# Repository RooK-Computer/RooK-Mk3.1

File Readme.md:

# RooK Mk3.1

RooK is a retro gaming console based on the Raspberry PI CM4/CM5. It has all the peripherials you need to be used as an old (modernish) console:

* HDMI for audio and video out.
* Barrel jack for 5V power input, because we love the simplicity of barrel jacks.
* an audio jack for, well... speakers!
* 4 USB ports for up to 4 modern gamepads.
* A cartridge slot!
* 3 Buttons to shut RooK down, exit the game and restart the game.

## How it all works

It's quite simple: instead of having an onboard SD card, the SD cards are installed onto separate PCBs for the cartridges. Once you put a cartridge in, RooK powers up and boots off the SD card in the cartridge.

Of course, unwrapping the SD cards can be tedious, so we built a cartridge reader.

It works out of the box with retropie, except for the three buttons. In this repository you find the software needed to enable those buttons. It's best done immediately after installing retropie, before you customize your setup.

## In this repository

There are 3 folders:

* software contains the sources for the .deb file to easily install overwatch and it's configuration. You'll find the .dep file in there as well, if you don't want to build it yourself. The source is compressed, as we have to ensure ownership and file privileges. Something git tends to ignore ;)
* PCBs contains all the designs for the PCBs involved: 
    * Cartridge - the PCB for cartridges
    * CartridgeReader - should be self-explanatory
    * KeyswitchCarrier - holds the switches for the three keys
    * Mainboard - the biggest of them.
    * Parts and CM4-Files are referenced in the aforementioned design files
* STLs contain the STL files for the case and the cartridge. You'll find our FreeCAD designs in there as well.

## I wanna build one!

Well for now, you have to produce and order the parts yourself. We're working on this. Stay tuned and keep an eye out at [rook.computer](https://rook.computer).

There is a building guide in the wiki.

## License

Unless noted otherwise this work is licensed under Creative Commons Attribution Share Alike 4.0 International.

`SPDX-License-Identifier:  CC-BY-SA-4.0`

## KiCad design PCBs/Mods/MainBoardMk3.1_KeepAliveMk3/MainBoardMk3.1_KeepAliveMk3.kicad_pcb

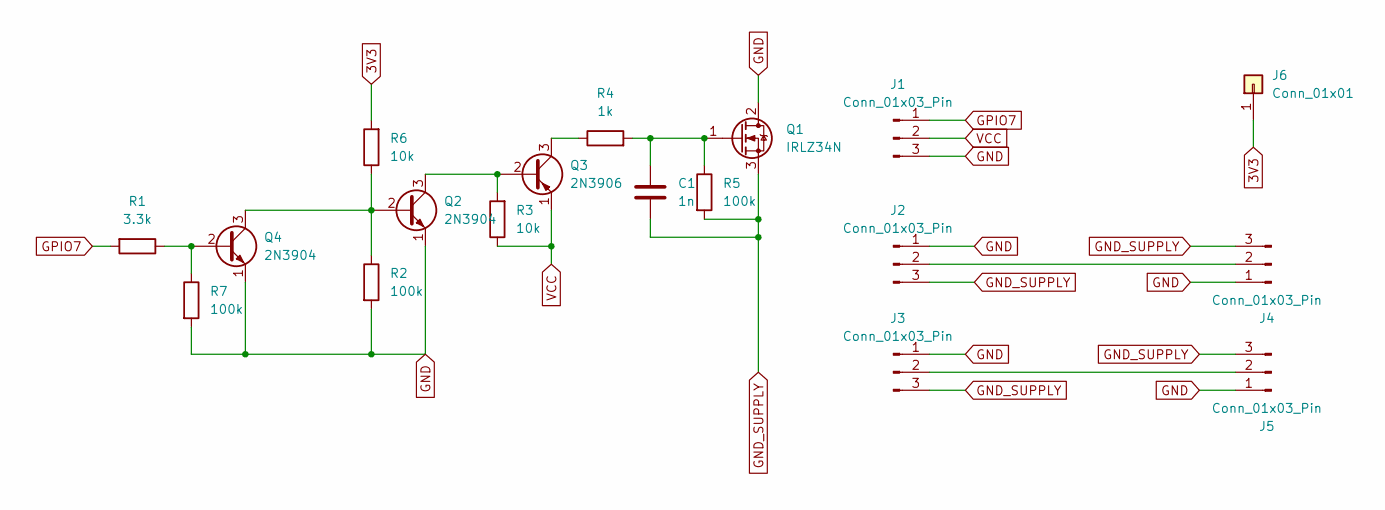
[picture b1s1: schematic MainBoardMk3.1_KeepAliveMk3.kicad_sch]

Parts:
C1: 1n; C_Disc_D5.0mm_W2.5mm_P2.50mm
J1, J2, J3: Conn_01x03_Pin; PinSocket_1x03_P2.54mm_Vertical
J4, J5: Conn_01x03_Pin; PinHeader_1x03_P2.54mm_Vertical
J6: Conn_01x01; SolderWire-0.5sqmm_1x01_D0.9mm_OD2.1mm
Q1: IRLZ34N; TO-220-3_Horizontal_TabDown
Q2, Q4: 2N3904; TO-92_HandSolder
Q3: 2N3906; TO-92_HandSolder
R1: 3.3k; R_Axial_DIN0207_L6.3mm_D2.5mm_P7.62mm_Horizontal
R2, R5, R7: 100k; R_Axial_DIN0207_L6.3mm_D2.5mm_P7.62mm_Horizontal
R3, R6: 10k; R_Axial_DIN0207_L6.3mm_D2.5mm_P7.62mm_Horizontal
R4: 1k; R_Axial_DIN0207_L6.3mm_D2.5mm_P7.62mm_Horizontal

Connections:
3V3: J6.1, R6.2
GND: J1.3, J2.1, J3.1, J4.1, J5.1, Q1.2 (D), Q2.1 (E), Q4.1 (E), R2.2, R7.2
GND_SUPPLY: C1.2, J2.3, J3.3, J4.3, J5.3, Q1.3 (S), R5.2
GPIO7: J1.1, R1.2
unnamed: J2.2, J4.2
unnamed: J3.2, J5.2
unnamed: C1.1, Q1.1 (G), R4.2, R5.1
unnamed: Q2.2 (B), Q4.3 (C), R2.1, R6.1
unnamed: Q2.3 (C), Q3.2 (B), R3.2
unnamed: Q3.3 (C), R4.1
unnamed: Q4.2 (B), R1.1, R7.1
VCC: J1.2, Q3.1 (E), R3.1

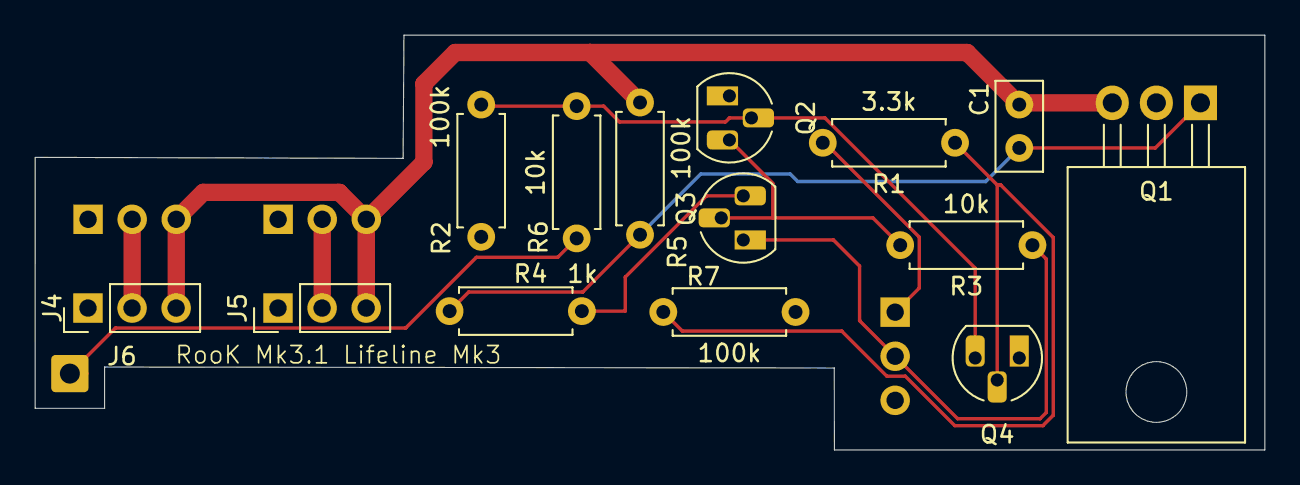
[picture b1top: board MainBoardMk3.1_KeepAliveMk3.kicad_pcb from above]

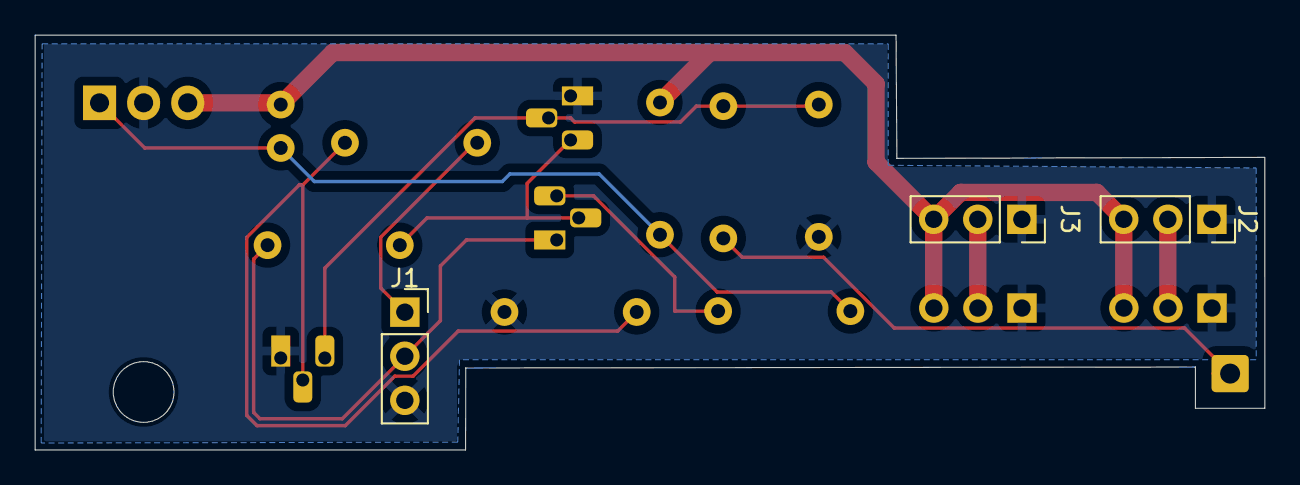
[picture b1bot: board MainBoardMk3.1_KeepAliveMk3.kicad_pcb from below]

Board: 2 copper layers, 70.8 x 23.9 mm, 18 parts (3 on the bottom side), 12 nets.

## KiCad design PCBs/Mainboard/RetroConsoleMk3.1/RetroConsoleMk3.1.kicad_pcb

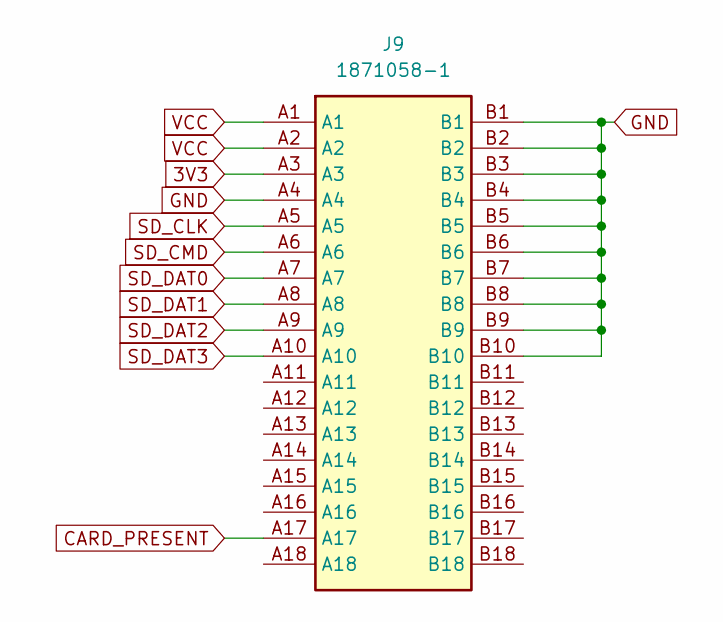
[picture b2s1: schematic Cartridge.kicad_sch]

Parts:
J9: 1871058-1; 18710581; Manufacturer_Part_Number 1871058-1; Mouser Part Number 571-1871058-1

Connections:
3V3: J9.A3; also elsewhere on the board
CARD_PRESENT: J9.A17; also elsewhere on the board
GND: J9.A4, J9.B1, J9.B2, J9.B3, J9.B4, J9.B5, J9.B6, J9.B7, J9.B8, J9.B9, J9.B10; also elsewhere on the board
SD_CLK: J9.A5; also elsewhere on the board
SD_CMD: J9.A6; also elsewhere on the board
SD_DAT0: J9.A7; also elsewhere on the board
SD_DAT1: J9.A8; also elsewhere on the board
SD_DAT2: J9.A9; also elsewhere on the board
SD_DAT3: J9.A10; also elsewhere on the board
VCC: J9.A1, J9.A2; also elsewhere on the board

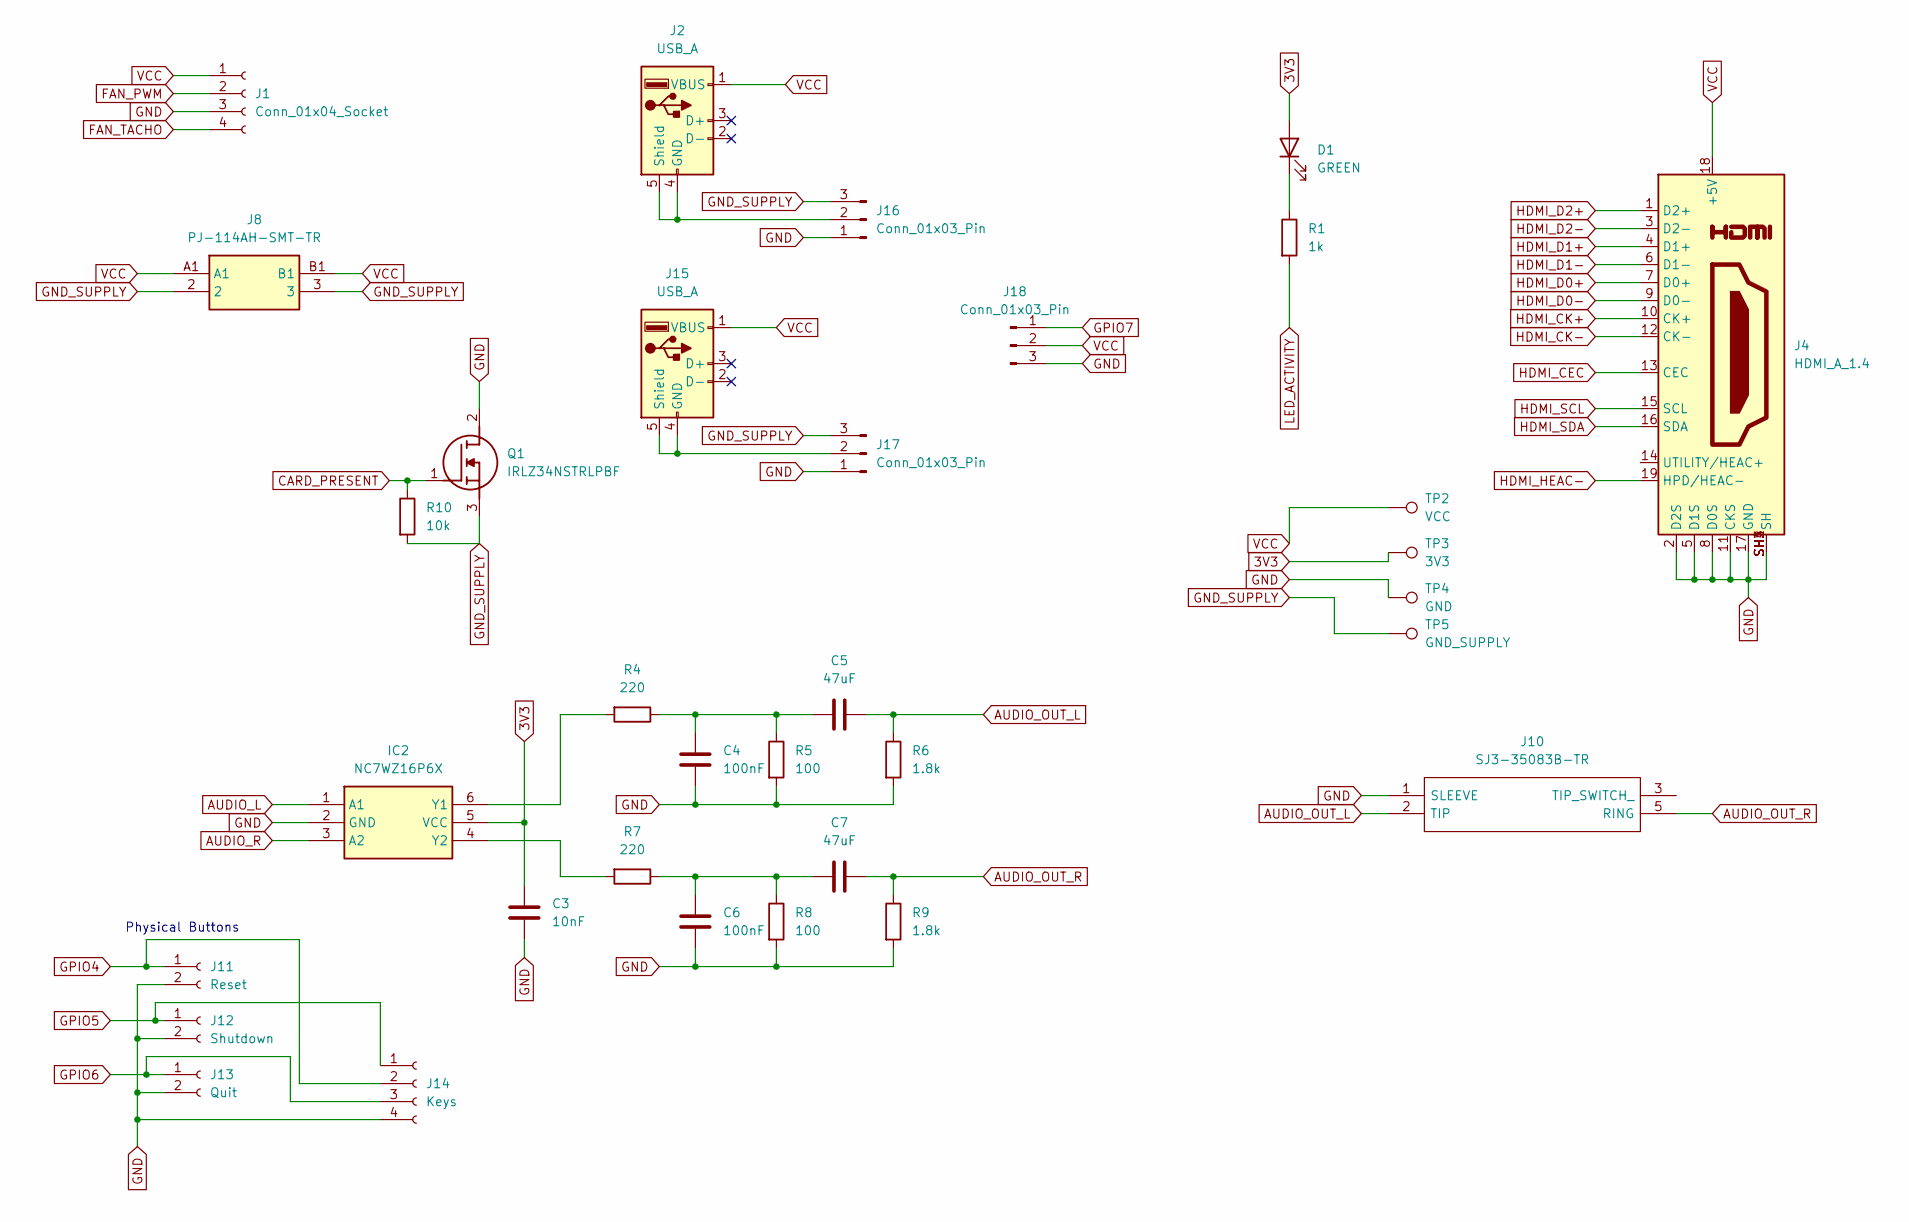
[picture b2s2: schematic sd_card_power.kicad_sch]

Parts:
C3: 10nF; C_0201_0603Metric
C4, C6: 100nF; C_0201_0603Metric
C5, C7: 47uF; C_1206_3216Metric
D1: GREEN; LED_0201_0603Metric
IC2: NC7WZ16P6X; SOT65P210X110-6N; Manufacturer_Part_Number NC7WZ16P6X; Mouser Part Number 512-NC7WZ16P6X
J1: Conn_01x04_Socket; JST_SH_BM04B-SRSS-TB_1x04-1MP_P1.00mm_Vertical
J2, J15: USB_A; USB_A_Wuerth_614004134726_Horizontal
J4: HDMI_A_1.4; HDMI_A_Molex_208658-1001_Horizontal
J8: PJ-114AH-SMT-TR; PJ114AHSMTTR; Manufacturer_Part_Number PJ-114AH-SMT-TR; Mouser Part Number 179-PJ-114AH-SMT-TR
J10: SJ3-35083B-TR; SJ335083BTR; Manufacturer_Part_Number SJ3-35083B-TR; Mouser Part Number 179-SJ3-35083B-TR
J11: Reset; JST_PH_B2B-PH-K_1x02_P2.00mm_Vertical
J12: Shutdown; JST_PH_B2B-PH-K_1x02_P2.00mm_Vertical
J13: Quit; JST_PH_B2B-PH-K_1x02_P2.00mm_Vertical
J14: Keys; JST_PH_B4B-PH-K_1x04_P2.00mm_Vertical
J16, J17, J18: Conn_01x03_Pin; PinHeader_1x03_P2.54mm_Vertical
Q1: IRLZ34NSTRLPBF; IRF2804STRLPBF; Manufacturer_Part_Number IRLZ34NSTRLPBF; Mouser Part Number 942-IRLZ34NSTRLPBF
R1: 1k; R_0201_0603Metric
R4, R7: 220; R_0201_0603Metric
R5, R8: 100; R_0201_0603Metric
R6, R9: 1.8k; R_0201_0603Metric
R10: 10k; R_0201_0603Metric
TP2: VCC; TestPoint_Pad_D3.0mm
TP3: 3V3; TestPoint_Pad_D3.0mm
TP4: GND; TestPoint_Pad_D3.0mm
TP5: GND_SUPPLY; TestPoint_Pad_D3.0mm

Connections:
3V3: C3.1, D1.2 (A), IC2.5 (VCC), TP3.1; also elsewhere on the board
AUDIO_L: IC2.1 (A1); also elsewhere on the board
AUDIO_OUT_L: C5.1, J10.2 (TIP), R6.1
AUDIO_OUT_R: C7.1, J10.5 (RING), R9.1
AUDIO_R: IC2.3 (A2); also elsewhere on the board
CARD_PRESENT: Q1.1 (G), R10.1; also elsewhere on the board
FAN_PWM: J1.2; also elsewhere on the board
FAN_TACHO: J1.4; also elsewhere on the board
GND: C3.2, C4.2, C6.2, IC2.2 (GND), J1.3, J4.2 (D2S), J4.5 (D1S), J4.8 (D0S), J4.11 (CKS), J4.17 (GND), J4.SH1 (SH), J4.SH2 (SH), J4.SH3 (SH), J4.SH4 (SH), J10.1 (SLEEVE), J11.2, J12.2, J13.2, J14.4, J16.1, J17.1, J18.3, Q1.2 (D), R5.2, R6.2, R8.2, R9.2, TP4.1; also elsewhere on the board
GND_SUPPLY: J8.2, J8.3, J16.3, J17.3, Q1.3 (S), R10.2, TP5.1
GPIO4: J11.1, J14.2; also elsewhere on the board
GPIO5: J12.1, J14.1; also elsewhere on the board
GPIO6: J13.1, J14.3; also elsewhere on the board
GPIO7: J18.1; also elsewhere on the board
HDMI_CEC: J4.13 (CEC); also elsewhere on the board
HDMI_CK+: J4.10 (CK+); also elsewhere on the board
HDMI_CK-: J4.12 (CK-); also elsewhere on the board
HDMI_D0+: J4.7 (D0+); also elsewhere on the board
HDMI_D0-: J4.9 (D0-); also elsewhere on the board
HDMI_D1+: J4.4 (D1+); also elsewhere on the board
HDMI_D1-: J4.6 (D1-); also elsewhere on the board
HDMI_D2+: J4.1 (D2+); also elsewhere on the board
HDMI_D2-: J4.3 (D2-); also elsewhere on the board
HDMI_HEAC-: J4.19 (HPD/HEAC-); also elsewhere on the board
HDMI_SCL: J4.15 (SCL); also elsewhere on the board
HDMI_SDA: J4.16 (SDA); also elsewhere on the board
LED_ACTIVITY: R1.2; also elsewhere on the board
unnamed: C4.1, C5.2, R4.1, R5.1
unnamed: C6.1, C7.2, R7.1, R8.1
unnamed: D1.1 (K), R1.1
unnamed: IC2.6 (Y1), R4.2
unnamed: IC2.4 (Y2), R7.2
unnamed: J15.4 (GND), J15.5 (Shield), J17.2
unnamed: J2.4 (GND), J2.5 (Shield), J16.2
VCC: J1.1, J2.1 (VBUS), J4.18 (+5V), J8.A1, J8.B1, J15.1 (VBUS), J18.2, TP2.1; also elsewhere on the board

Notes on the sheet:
Physical Buttons

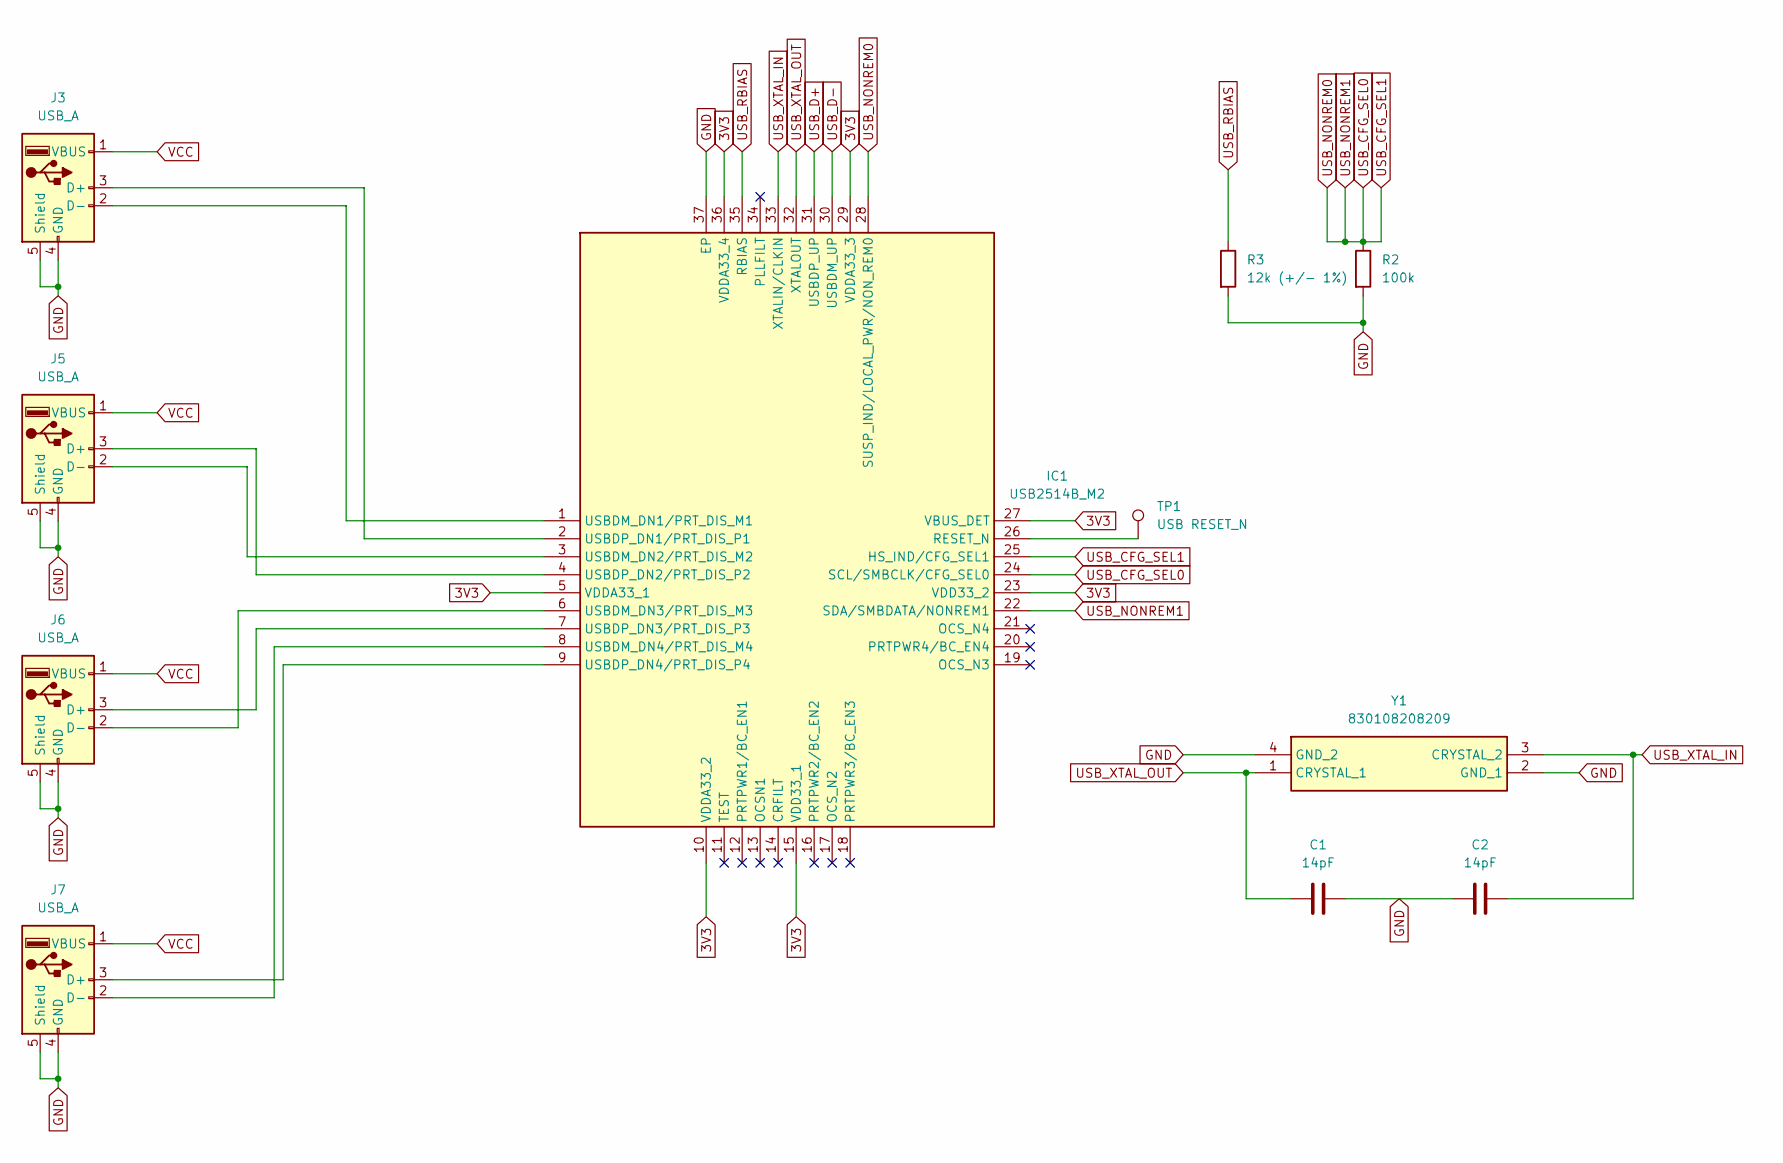
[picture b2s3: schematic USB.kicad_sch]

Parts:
C1, C2: 14pF; C_0201_0603Metric
IC1: USB2514B_M2; QFN50P600X600X100-37N-D; Manufacturer_Part_Number USB2514B/M2; Mouser Part Number 579-USB2514B/M2
J3, J5, J6, J7: USB_A; USB_A_Molex_67643_Horizontal
R2: 100k; R_0201_0603Metric
R3: 12k (+/- 1%); R_0201_0603Metric
TP1: USB RESET_N; TestPoint_Pad_D3.0mm
Y1: 830108208209; Manufacturer_Part_Number 830108208209; Mouser Part Number 710-830108208209

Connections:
3V3: IC1.5 (VDDA33_1), IC1.10 (VDDA33_2), IC1.15 (VDD33_1), IC1.23 (VDD33_2), IC1.27 (VBUS_DET), IC1.29 (VDDA33_3), IC1.36 (VDDA33_4); also elsewhere on the board
GND: C1.1, C2.2, IC1.37 (EP), J3.4 (GND), J3.5 (Shield), J5.4 (GND), J5.5 (Shield), J6.4 (GND), J6.5 (Shield), J7.4 (GND), J7.5 (Shield), R2.2, R3.2, Y1.2 (GND_1), Y1.4 (GND_2); also elsewhere on the board
unnamed: IC1.26 (RESET_N), TP1.1
unnamed: IC1.1 (USBDM_DN1/PRT_DIS_M1), J3.2 (D-)
unnamed: IC1.3 (USBDM_DN2/PRT_DIS_M2), J5.2 (D-)
unnamed: IC1.6 (USBDM_DN3/PRT_DIS_M3), J6.2 (D-)
unnamed: IC1.8 (USBDM_DN4/PRT_DIS_M4), J7.2 (D-)
unnamed: IC1.2 (USBDP_DN1/PRT_DIS_P1), J3.3 (D+)
unnamed: IC1.4 (USBDP_DN2/PRT_DIS_P2), J5.3 (D+)
unnamed: IC1.7 (USBDP_DN3/PRT_DIS_P3), J6.3 (D+)
unnamed: IC1.9 (USBDP_DN4/PRT_DIS_P4), J7.3 (D+)
USB_CFG_SEL0: IC1.22 (SDA/SMBDATA/NONREM1), IC1.24 (SCL/SMBCLK/CFG_SEL0), IC1.25 (HS_IND/CFG_SEL1), IC1.28 (SUSP_IND/LOCAL_PWR/NON_REM0), R2.1
USB_D+: IC1.31 (USBDP_UP); also elsewhere on the board
USB_D-: IC1.30 (USBDM_UP); also elsewhere on the board
USB_RBIAS: IC1.35 (RBIAS), R3.1
USB_XTAL_IN: C2.1, IC1.33 (XTALIN/CLKIN), Y1.3 (CRYSTAL_2)
USB_XTAL_OUT: C1.2, IC1.32 (XTALOUT), Y1.1 (CRYSTAL_1)
VCC: J3.1 (VBUS), J5.1 (VBUS), J6.1 (VBUS), J7.1 (VBUS); also elsewhere on the board

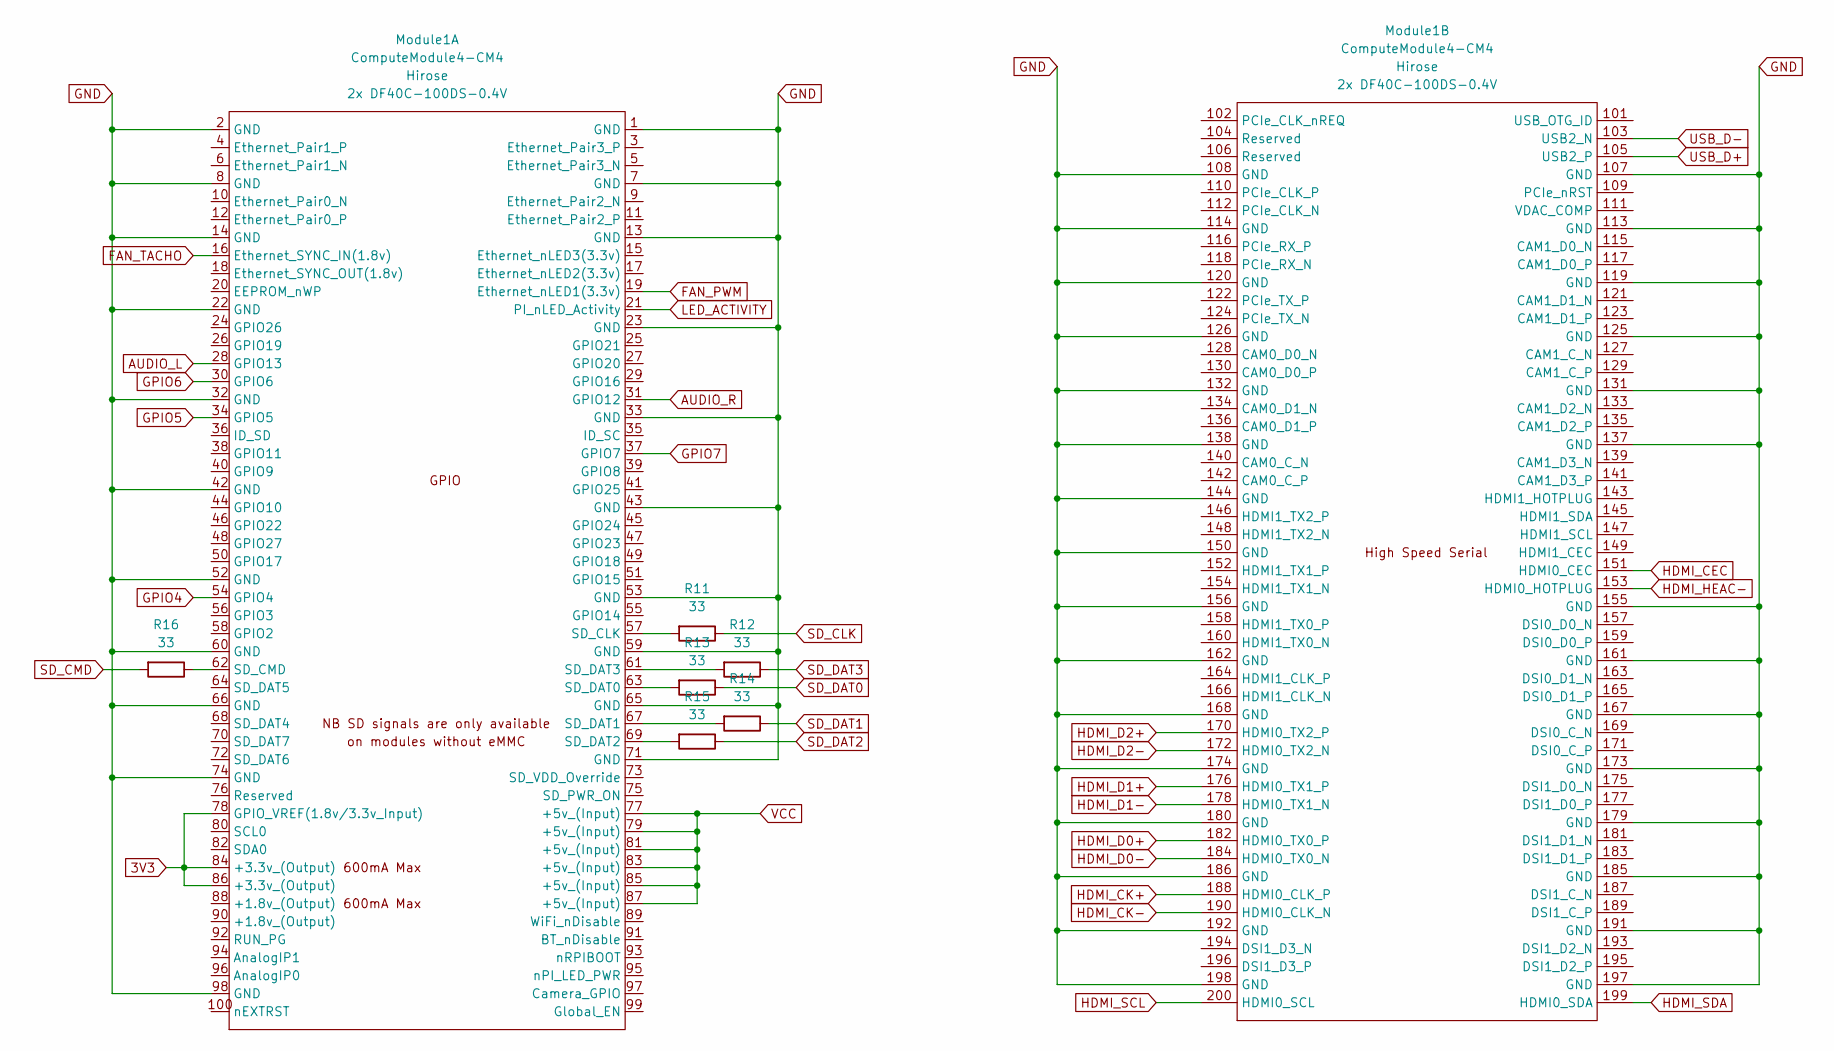
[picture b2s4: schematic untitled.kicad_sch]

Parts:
Module1: ComputeModule4-CM4; Raspberry-Pi-4-Compute-Module
R11, R12, R13, R14, R15, R16: 33; R_0201_0603Metric

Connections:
3V3: Module1.78 (GPIO_VREF(1.8v/3.3v_Input)), Module1.84 (+3.3v_(Output)), Module1.86 (+3.3v_(Output)); also elsewhere on the board
AUDIO_L: Module1.28 (GPIO13); also elsewhere on the board
AUDIO_R: Module1.31 (GPIO12); also elsewhere on the board
FAN_PWM: Module1.19 (Ethernet_nLED1(3.3v)); also elsewhere on the board
FAN_TACHO: Module1.16 (Ethernet_SYNC_IN(1.8v)); also elsewhere on the board
GND: Module1.1 (GND), Module1.2 (GND), Module1.7 (GND), Module1.8 (GND), Module1.13 (GND), Module1.14 (GND), Module1.22 (GND), Module1.23 (GND), Module1.32 (GND), Module1.33 (GND), Module1.42 (GND), Module1.43 (GND), Module1.52 (GND), Module1.53 (GND), Module1.59 (GND), Module1.60 (GND), Module1.65 (GND), Module1.66 (GND), Module1.71 (GND), Module1.74 (GND), Module1.98 (GND), Module1.107 (GND), Module1.108 (GND), Module1.113 (GND), Module1.114 (GND), Module1.119 (GND), Module1.120 (GND), Module1.125 (GND), Module1.126 (GND), Module1.131 (GND), Module1.132 (GND), Module1.137 (GND), Module1.138 (GND), Module1.144 (GND), Module1.150 (GND), Module1.155 (GND), Module1.156 (GND), Module1.161 (GND), Module1.162 (GND), Module1.167 (GND), Module1.168 (GND), Module1.173 (GND), Module1.174 (GND), Module1.179 (GND), Module1.180 (GND), Module1.185 (GND), Module1.186 (GND), Module1.191 (GND), Module1.192 (GND), Module1.197 (GND), Module1.198 (GND); also elsewhere on the board
GPIO4: Module1.54 (GPIO4); also elsewhere on the board
GPIO5: Module1.34 (GPIO5); also elsewhere on the board
GPIO6: Module1.30 (GPIO6); also elsewhere on the board
GPIO7: Module1.37 (GPIO7); also elsewhere on the board
HDMI_CEC: Module1.151 (HDMI0_CEC); also elsewhere on the board
HDMI_CK+: Module1.188 (HDMI0_CLK_P); also elsewhere on the board
HDMI_CK-: Module1.190 (HDMI0_CLK_N); also elsewhere on the board
HDMI_D0+: Module1.182 (HDMI0_TX0_P); also elsewhere on the board
HDMI_D0-: Module1.184 (HDMI0_TX0_N); also elsewhere on the board
HDMI_D1+: Module1.176 (HDMI0_TX1_P); also elsewhere on the board
HDMI_D1-: Module1.178 (HDMI0_TX1_N); also elsewhere on the board
HDMI_D2+: Module1.170 (HDMI0_TX2_P); also elsewhere on the board
HDMI_D2-: Module1.172 (HDMI0_TX2_N); also elsewhere on the board
HDMI_HEAC-: Module1.153 (HDMI0_HOTPLUG); also elsewhere on the board
HDMI_SCL: Module1.200 (HDMI0_SCL); also elsewhere on the board
HDMI_SDA: Module1.199 (HDMI0_SDA); also elsewhere on the board
LED_ACTIVITY: Module1.21 (PI_nLED_Activity); also elsewhere on the board
unnamed: Module1.57 (SD_CLK), R11.2
unnamed: Module1.62 (SD_CMD), R16.1
unnamed: Module1.63 (SD_DAT0), R13.2
unnamed: Module1.67 (SD_DAT1), R14.2
unnamed: Module1.69 (SD_DAT2), R15.2
unnamed: Module1.61 (SD_DAT3), R12.2
SD_CLK: R11.1; also elsewhere on the board
SD_CMD: R16.2; also elsewhere on the board
SD_DAT0: R13.1; also elsewhere on the board
SD_DAT1: R14.1; also elsewhere on the board
SD_DAT2: R15.1; also elsewhere on the board
SD_DAT3: R12.1; also elsewhere on the board
USB_D+: Module1.105 (USB2_P); also elsewhere on the board
USB_D-: Module1.103 (USB2_N); also elsewhere on the board
VCC: Module1.77 (+5v_(Input)), Module1.79 (+5v_(Input)), Module1.81 (+5v_(Input)), Module1.83 (+5v_(Input)), Module1.85 (+5v_(Input)), Module1.87 (+5v_(Input)); also elsewhere on the board

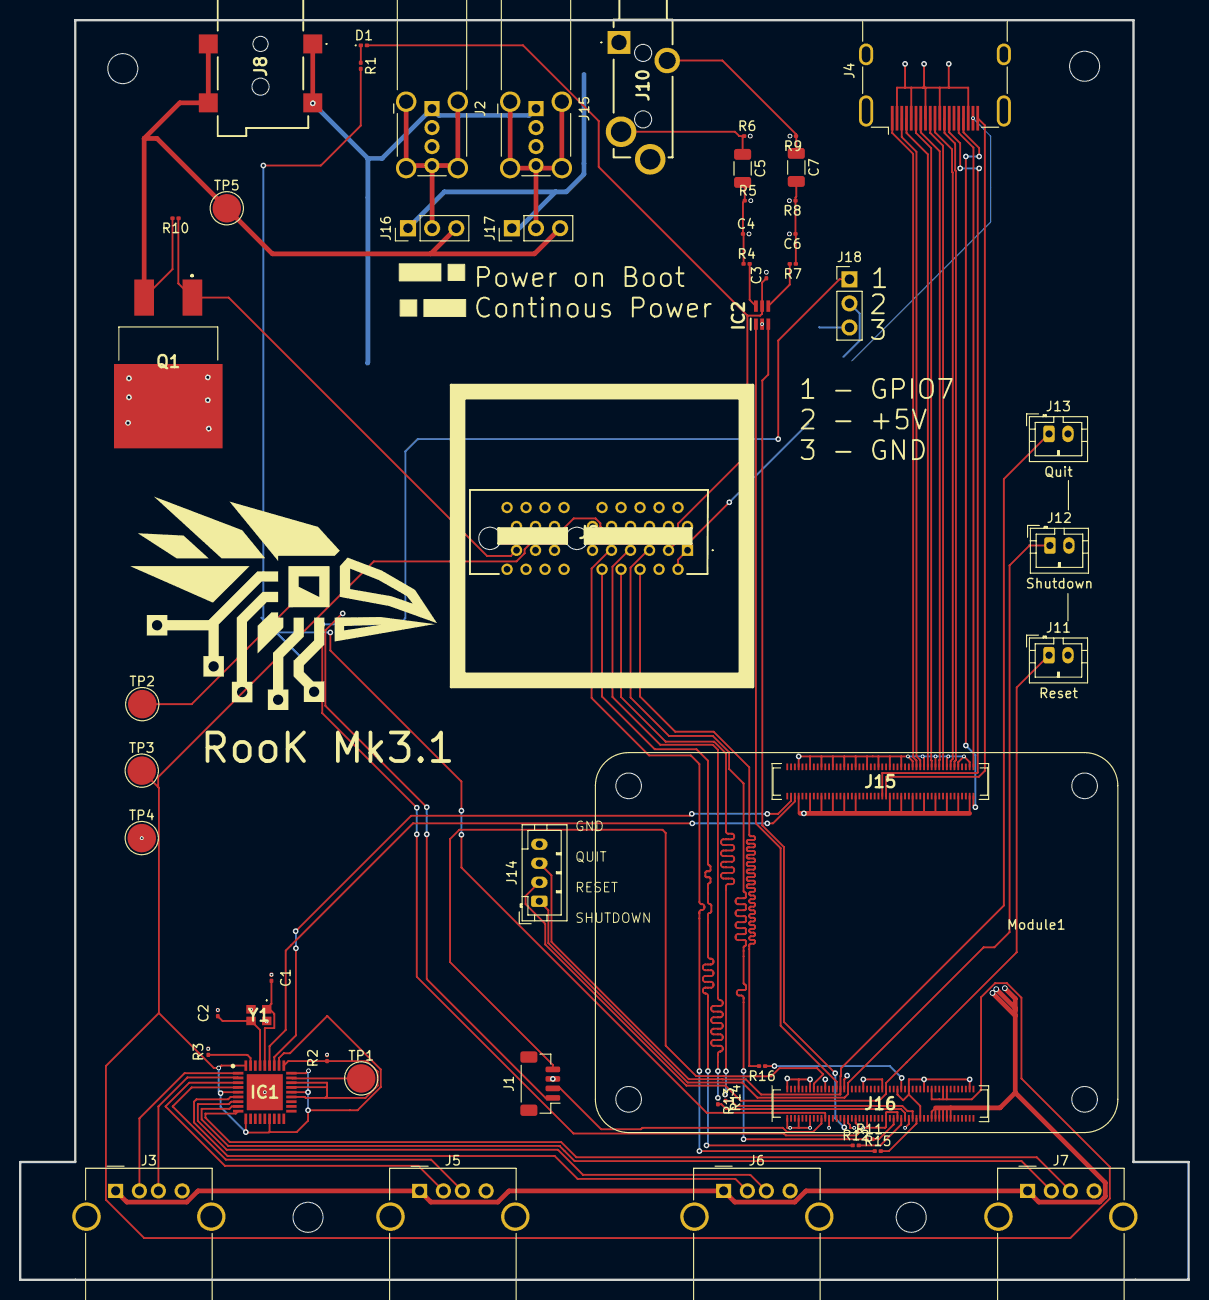
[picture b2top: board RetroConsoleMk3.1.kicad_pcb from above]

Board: 2 copper layers, 123.0 x 132.6 mm, 54 parts (0 on the bottom side), 62 nets.

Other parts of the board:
J15#2, J16#2: DF40C100DS04V51

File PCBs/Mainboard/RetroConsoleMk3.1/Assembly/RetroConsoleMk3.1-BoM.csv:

Id;Designator;Footprint;Quantity;Designation;Supplier and ref;;
1;R13,R12,R15,R11,R14,R16;R_0201_0603Metric;6;33;;;
3;C3;C_0201_0603Metric;1;10nF;;;
4;J7,J5,J6,J3;USB_A_Molex_67643_Horizontal;4;USB_A;https://www.molex.com/en-us/products/part-detail/676432911;;
5;C7,C5;C_1206_3216Metric;2;47uF;;;
6;J10;SJ335083BTR;1;SJ3-35083B-TR;https://www.mouser.de/ProductDetail/Same-Sky/SJ3-35083B-TR?q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;;
7;J16,J15;DF40C100DS04V51;2;DF40C100DS04V51;https://www.hirose.com/product/p/CL0684-4033-4-51?lang=en#;;
8;J8;PJ114AHSMTTR;1;PJ-114AH-SMT-TR;https://www.mouser.de/ProductDetail/Same-Sky/PJ-114AH-SMT-TR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;;
9;R7,R4;R_0201_0603Metric;2;220;;;
10;Y1;830108208209;1;830108208209;https://www.mouser.de/ProductDetail/Wurth-Elektronik/8301082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;;
11;R1;R_0201_0603Metric;1;1k;;;
13;R5,R8;R_0201_0603Metric;2;100;;;
14;IC2;SOT65P210X110-6N;1;NC7WZ16P6X;https://www.mouser.de/ProductDetail/onsemi-Fairchild/NC7WZ16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;;
15;R6,R9;R_0201_0603Metric;2;1.8k;;;
17;D1;LED_0201_0603Metric;1;GREEN;;;
18;C6,C4;C_0201_0603Metric;2;100nF;;;
20;R10;R_0201_0603Metric;1;10k;;;
21;C1,C2;C_0201_0603Metric;2;14pF;;;
23;J9;18710581;1;1871058-1;https://www.mouser.de/ProductDetail/TE-Connectivity/1871058-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;;
24;J4;HDMI_A_Molex_208658-1001_Horizontal;1;HDMI_A_1.4;;;
25;Q1;IRF2804STRLPBF;1;IRLZ34NSTRLPBF;https://www.mouser.de/ProductDetail/Infineon-Technologies/IR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;;
26;J14;JST_PH_B4B-PH-K_1x04_P2.00mm_Vertical;1;Keys;;;
28;J1;JST_SH_BM04B-SRSS-TB_1x04-1MP_P1.00mm_Vertical;1;Conn_01x04_Socket;;;
29;R2;R_0201_0603Metric;1;100k;;;
30;R3;R_0201_0603Metric;1;12k (+/- 1%);;;
31;IC1;QFN50P600X600X100-37N-D;1;USB2514B_M2;https://www.mouser.de/ProductDetail/Microchip-Technology/USB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;;

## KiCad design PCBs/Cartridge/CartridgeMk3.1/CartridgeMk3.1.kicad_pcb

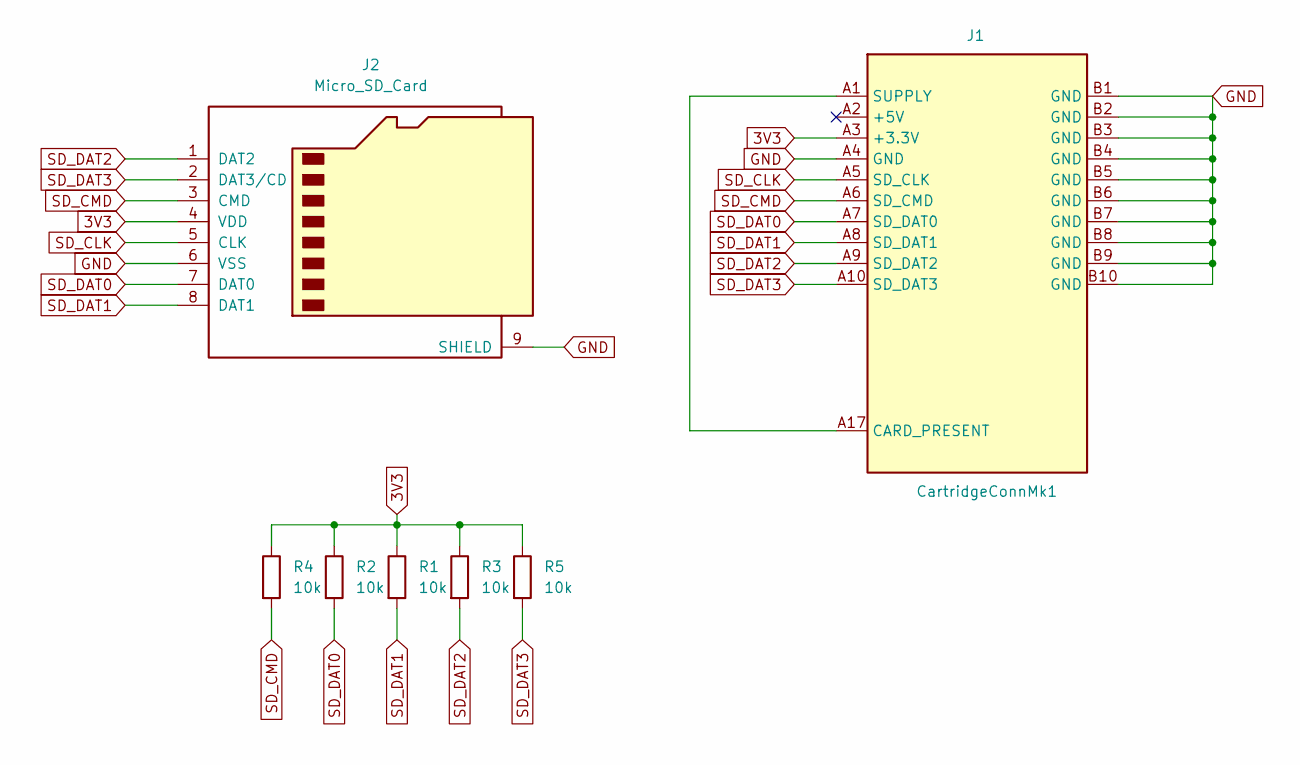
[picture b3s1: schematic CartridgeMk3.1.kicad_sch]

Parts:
J1: CartridgeConnMk1; BUS_PCIexpress_x1
J2: Micro_SD_Card; SDCARD_MOLEX_503398-1892
R1, R2, R3, R4, R5: 10k; R_0201_0603Metric

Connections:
3V3: J1.A3 (+3.3V), J2.4 (VDD), R1.1, R2.1, R3.1, R4.1, R5.1
GND: J1.A4 (GND), J1.B1 (GND), J1.B2 (GND), J1.B3 (GND), J1.B4 (GND), J1.B5 (GND), J1.B6 (GND), J1.B7 (GND), J1.B8 (GND), J1.B9 (GND), J1.B10 (GND), J2.6 (VSS), J2.9 (SHIELD)
unnamed: J1.A1 (SUPPLY), J1.A17 (CARD_PRESENT)
SD_CLK: J1.A5 (SD_CLK), J2.5 (CLK)
SD_CMD: J1.A6 (SD_CMD), J2.3 (CMD), R4.2
SD_DAT0: J1.A7 (SD_DAT0), J2.7 (DAT0), R2.2
SD_DAT1: J1.A8 (SD_DAT1), J2.8 (DAT1), R1.2
SD_DAT2: J1.A9 (SD_DAT2), J2.1 (DAT2), R3.2
SD_DAT3: J1.A10 (SD_DAT3), J2.2 (DAT3/CD), R5.2

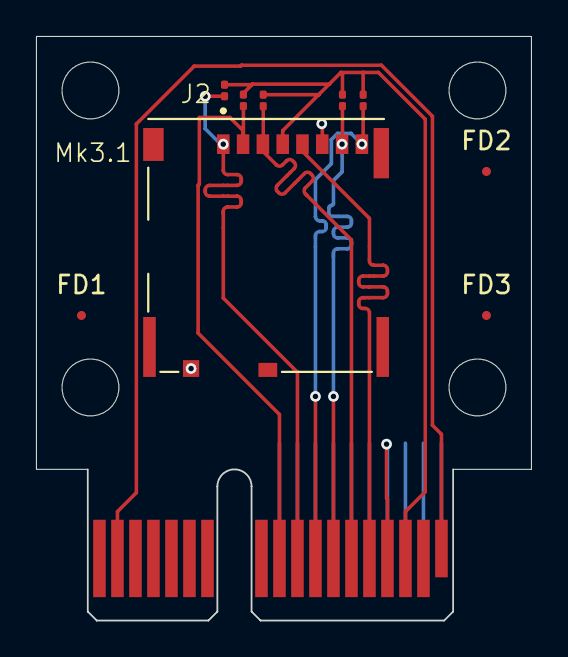
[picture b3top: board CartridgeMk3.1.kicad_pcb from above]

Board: 2 copper layers, 27.5 x 32.5 mm, 10 parts (1 on the bottom side), 9 nets.

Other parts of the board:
FD1, FD2, FD3: Fiducial_0.5mm_Mask1.5mm

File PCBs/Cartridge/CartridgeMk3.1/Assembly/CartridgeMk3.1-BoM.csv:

Id;Designator;Footprint;Quantity;Designation;Supplier and ref;;
2;R1,R3,R5,R2,R4;R_0201_0603Metric;5;10k;;;
3;J2;SDCARD_MOLEX_503398-1892;1;Micro_SD_Card;;;

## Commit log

2025-09-27 updated button pieces
2025-12-22 Updated Repo with files for Mk3.1 content
2025-12-25 updated backpanel
2026-01-14 Add LICENSE
2026-01-23 added the Lifeline PCB
2026-01-30 added STL file for BackPanel with Antenna hole.
2026-03-29 added a different back panel with internal holding of the antenna
